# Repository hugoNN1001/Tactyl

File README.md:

# Tactyl

Tactyl is a gesture-based typing interface that lets you type anywhere without a keyboard. It converts finger taps into digital characters, avoiding the fixed workspace and repetitive wrist/hand positioning that conventional keyboards require.

## Photos

.jpg)

## How It Works

Tactyl uses a **five-bit chorded input** scheme: each of the five fingers acts as one bit. Tapping different finger combinations produces unique 5-bit codes, which are mapped in software to characters and commands. This gives 32 possible combinations enough to cover the full alphabet.

Finger movement is tracked by five IMUs (one per finger) embedded in the glove, allowing the system to distinguish intentional taps from general hand motion. Sensor data is processed by an ESP32-based embedded controller and transmitted wirelessly to a host computer. A haptic feedback system provides confirmation of typed characters and connection status.

## System Architecture

**Sensing layer.** Five **IMUs**, one per finger, each measuring acceleration to detect individual finger taps independently. Since they all share the same I²C address, a **TCA9548A I²C multiplexer** separates them into independent channels to faciliate communication.

**Power.** A **BQ24074 linear charge management IC** handles Li-ion battery charging while supporting system load via its **power-path output**. Charge current (300mA/500 mA) is selectable via solder jumpers. **Reverse polarity protection** is implemented with a P-FET with a **G-S protection diode**. The 3.3 V rail is generated by a **AP2112 LDO**. A **MAX17048 fuel gauge** monitors voltage/SOC over I²C and asserts an ALERT interrupt for **low-battery detection**, feeding the firmware's haptic alert logic. Main power traces were sized appropriate to handle the expected load. 

**Programming.** A **CP2102 USB-UART bridge** converts USB differential signals to UART to program the ESP32. Differential traces are kept short and **sized to 90Ω impedance**. ESD protection diodes are placed as close to the USB-C connector as possible.

**Processing.** An **ESP32-S3 microcontroller** processes sensor inputs, runs tap detection, maintains the five-bit finger state register, performs chord recognition, and manages communication with the host device. Each completed chord is looked up in a table and converted into the corresponding character. An **auto-program circuit** is also implemented with a pair to MOSFETs to automatically trigger BOOT & RST when programming.

**Wireless communication.** The interpreted character is transmitted over **Bluetooth Low Energy (BLE)** from the ESP32-S3 to the host device. The antenna keep-out section is kept clear of any copper.

**Haptic feedback.** A vibration motor, driven by a **DRV2605L haptic driver**, gives the user tactile confirmation of events such as BLE connection/disconnection state and low power. An **ERM coin vibration motor** is mounted through **strain-relief holes** on the main PCB. For the next version, a better decoupling capacitor should be added to prevent the ESP from resetting during strong motor vibrations.

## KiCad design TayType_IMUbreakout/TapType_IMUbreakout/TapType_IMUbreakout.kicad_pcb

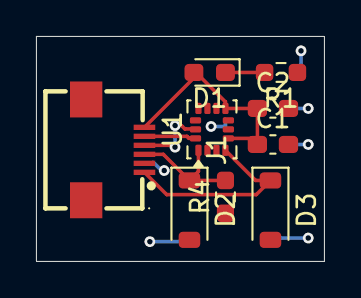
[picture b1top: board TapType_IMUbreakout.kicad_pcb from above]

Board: 2 copper layers, 16.0 x 12.5 mm, 9 parts (0 on the bottom side), 7 nets.

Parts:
C1, C2: 100nF; C_0603_1608Metric_Pad1.08x0.95mm_HandSolder
D1: LED; LED_0603_1608Metric_Pad1.05x0.95mm_HandSolder
D2, D3: SMF5.0A; D_SOD-123
J1: Conn_01x06; FPC-SMD_6P-P0.50_FPC-05FB-6PH20
R1: 220R; R_0603_1608Metric_Pad0.98x0.95mm_HandSolder
R4: 10k; R_0603_1608Metric_Pad0.98x0.95mm_HandSolder
U1: LSM6DS3; LGA-14_3x2.5mm_P0.5mm_LayoutBorder3x4y

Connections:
+3.3V: C1.1, C2.1, D1.2 (A), J1.6, U1.5 (VDDIO), U1.8 (VDD)
/INT1: D3.1, J1.1, U1.4 (INT1)
/SA0: D2.1, J1.3, R4.2, U1.1 (SDO/SA0)
/SCL: J1.4, U1.13 (SCL)
/SDA: J1.5, U1.14 (SDA)
GND: C1.2, C2.2, D2.2, D3.2, J1.2, R1.1, R4.1, U1.6 (GND), U1.7 (GND)
unnamed: D1.1 (K), R1.2

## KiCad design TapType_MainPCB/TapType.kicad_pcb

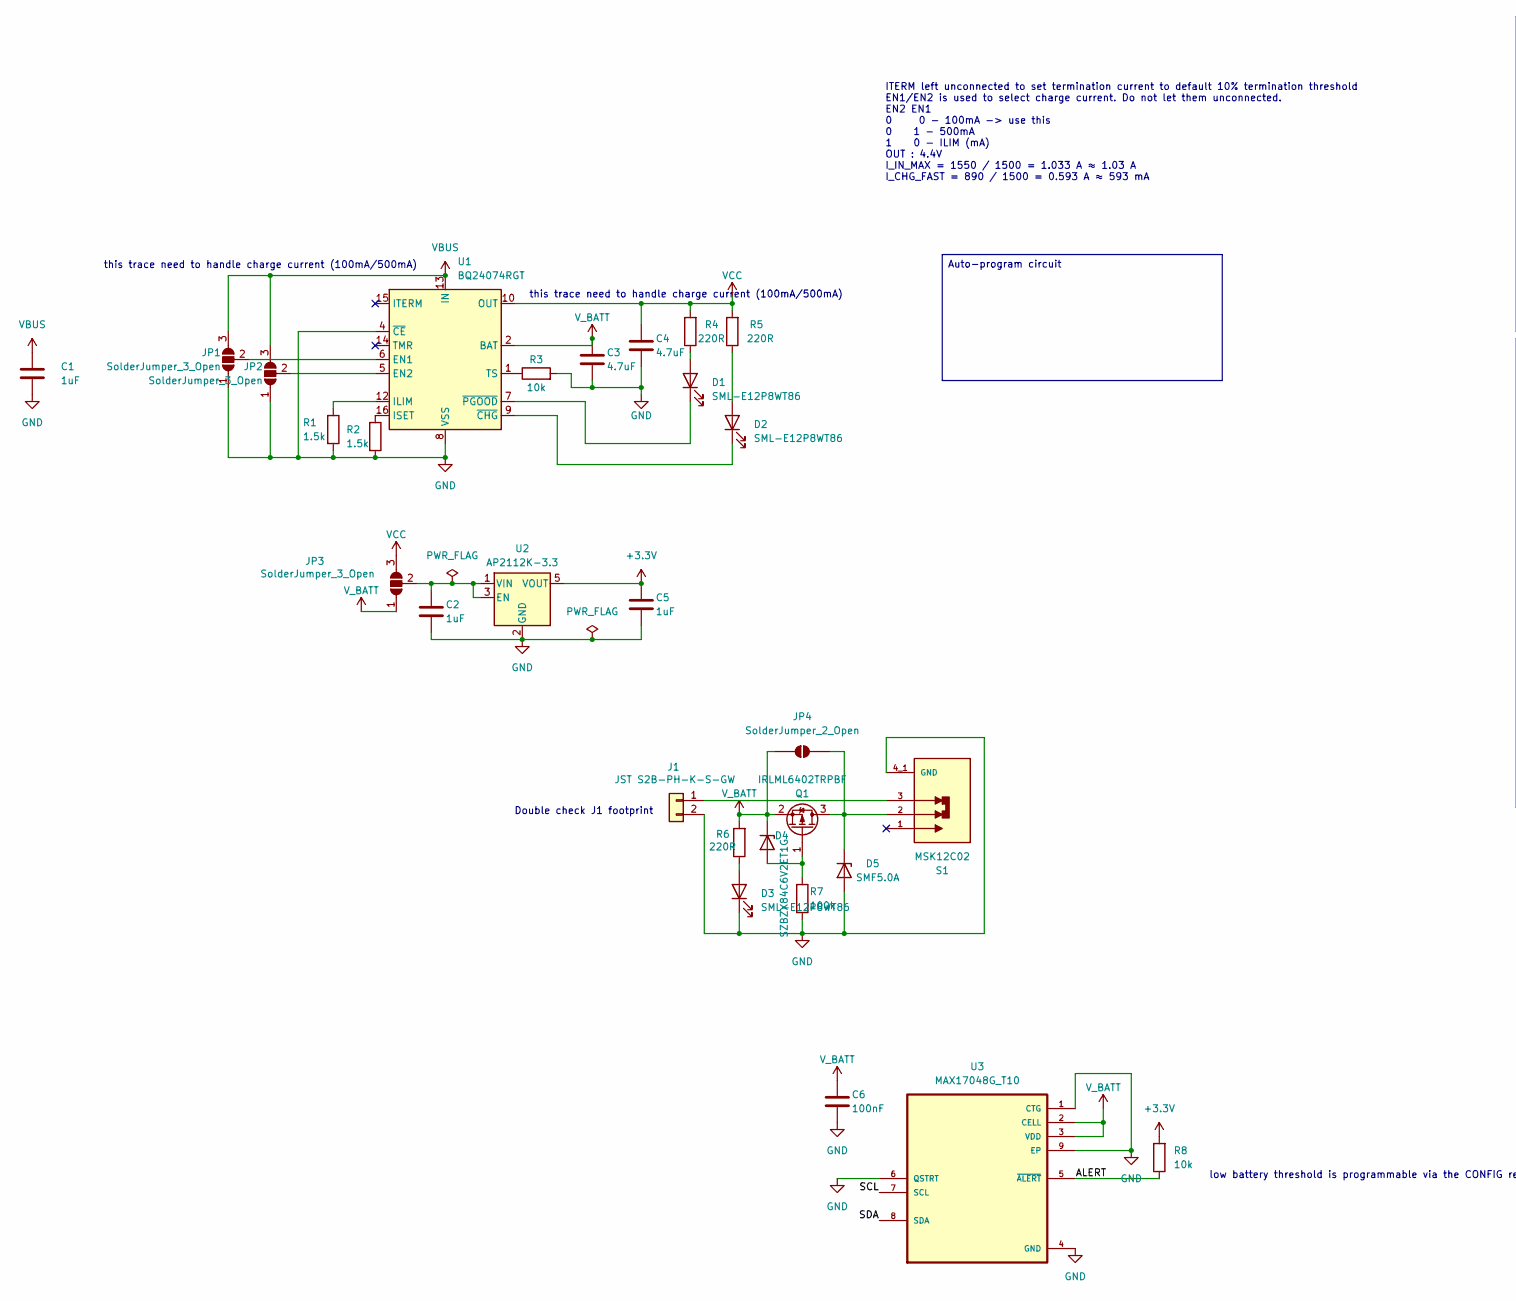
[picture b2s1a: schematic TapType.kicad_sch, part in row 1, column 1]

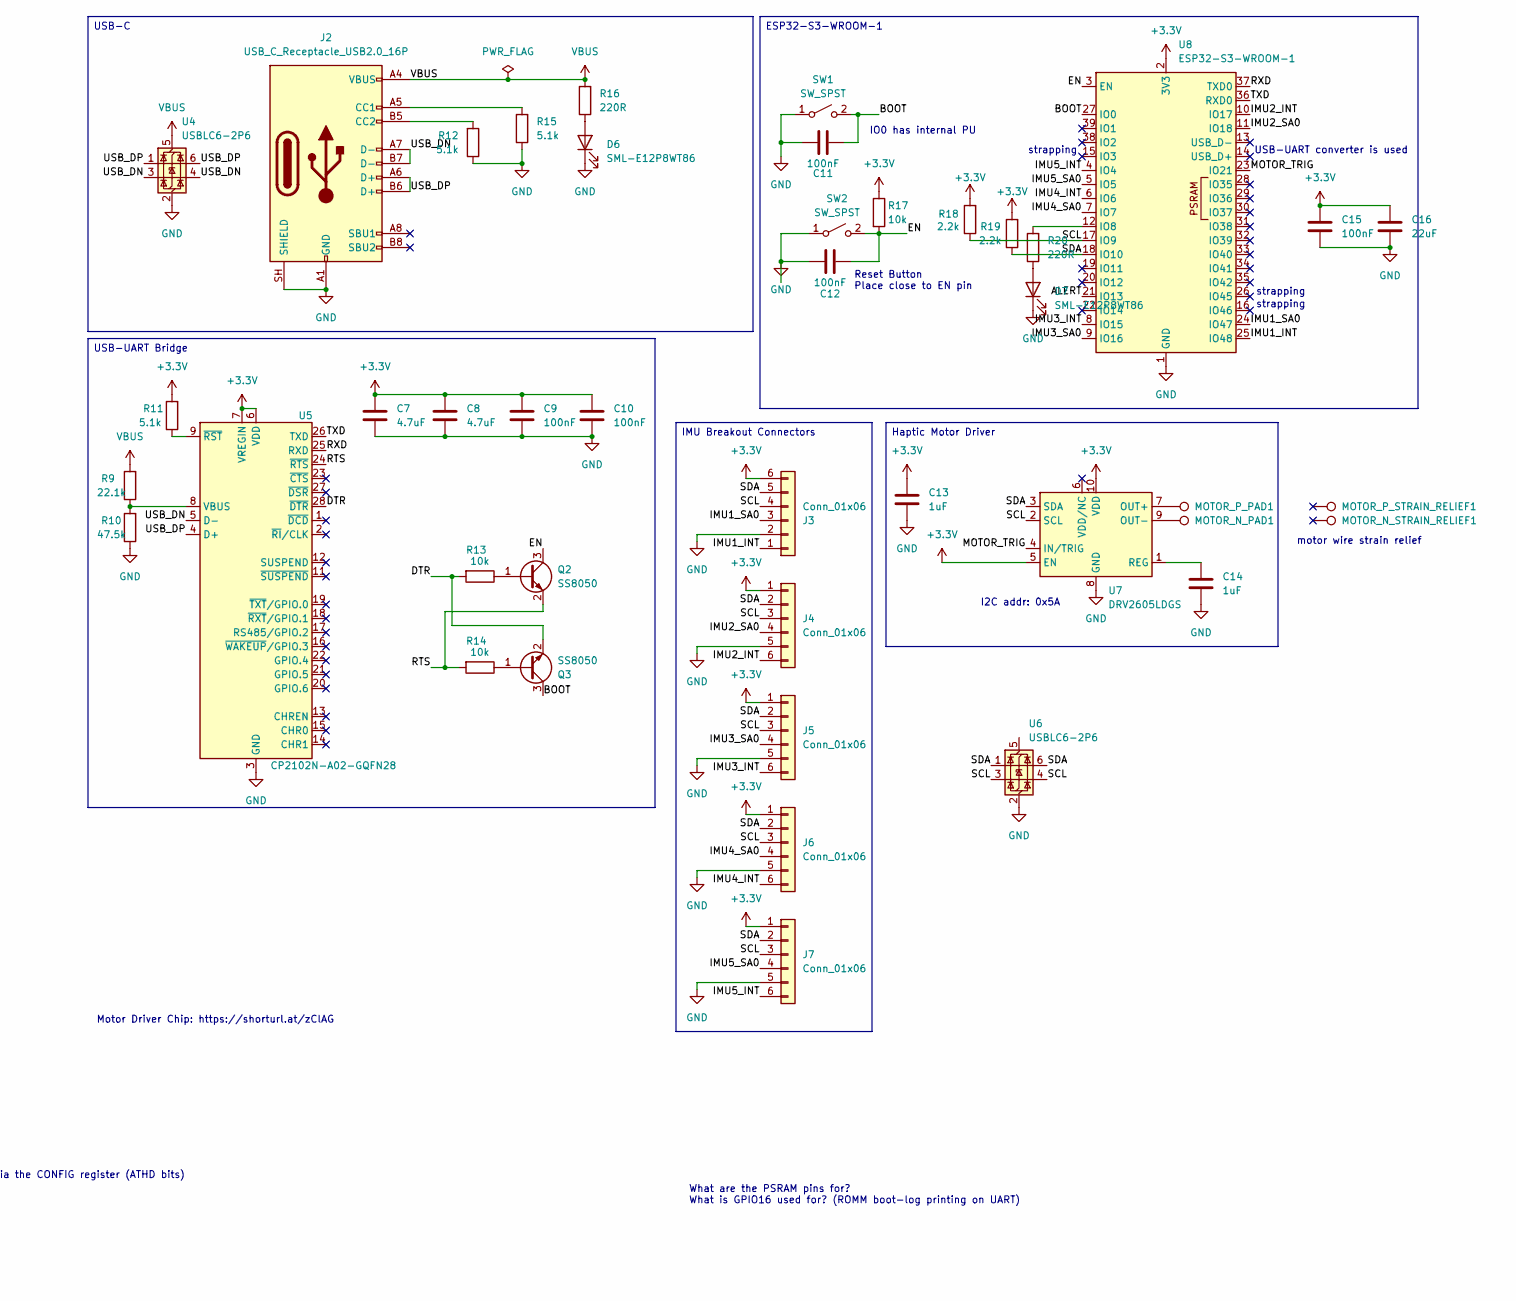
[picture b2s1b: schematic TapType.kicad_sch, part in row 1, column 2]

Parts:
C1, C2, C5, C13, C14: 1uF; C_0603_1608Metric
C3, C4, C7, C8: 4.7uF; C_0603_1608Metric
C6, C9, C10, C11, C12, C15: 100nF; C_0603_1608Metric
C16: 22uF; C_0603_1608Metric
D1, D2, D3, D6, D7: SML-E12P8WT86; D_0603_1608Metric
D4: SZBZX84C6V2ET1G; SOD-123_L2.7-W1.6-LS3.7-RD
D5: SMF5.0A; D_SOD-123F
J1: JST S2B-PH-K-S-GW; CONN-TH_S2B-PH-K-S-GW
J2: USB_C_Receptacle_USB2.0_16P; TYPE-C-SMD_SBC-160S1A-20-S412
J3, J4, J5, J6, J7: Conn_01x06; FPC-SMD_6P-P0.50_FPC-05FB-6PH20
JP1, JP2, JP3: SolderJumper_3_Open; SolderJumper-3_P2.0mm_Open_TrianglePad1.0x1.5mm
JP4: SolderJumper_2_Open; SolderJumper-2_P1.3mm_Open_TrianglePad1.0x1.5mm
MOTOR_N_PAD1: TestPoint; TestPoint_Pad_D2.0mm
MOTOR_N_STRAIN_RELIEF1: TestPoint; strain relief
MOTOR_P_PAD1: TestPoint; TestPoint_Pad_D2.0mm
MOTOR_P_STRAIN_RELIEF1: TestPoint; strain relief
Q1: IRLML6402TRPBF; SOT-23
Q2, Q3: SS8050; SOT-23
R1, R2: 1.5k; R_0603_1608Metric
R3, R8, R13, R14, R17: 10k; R_0603_1608Metric
R4, R5, R6, R16, R20: 220R; R_0603_1608Metric
R7: 100k; R_0603_1608Metric
R9: 22.1k; R_0603_1608Metric
R10: 47.5k; R_0603_1608Metric
R11, R12, R15: 5.1k; R_0603_1608Metric
R18, R19: 2.2k; R_0603_1608Metric
S1: MSK12C02; SW-SMD_G-SWITCH_MK-12C02-G015; PARTREV A/0
SW1, SW2: SW_SPST; KEY-SMD_B3U-1000PM
U1: BQ24074RGT; VQFN-16-1EP_3x3mm_P0.5mm_EP1.6x1.6mm
U2: AP2112K-3.3; SOT-23-5
U3: MAX17048G_T10; SON50P200X200X80-9N
U4, U6: USBLC6-2P6; SOT-666
U5: CP2102N-A02-GQFN28; QFN-28-1EP_5x5mm_P0.5mm_EP3.35x3.35mm
U7: DRV2605LDGS; TSSOP-10_3x3mm_P0.5mm
U8: ESP32-S3-WROOM-1

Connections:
+3.3V: C5.1, C7.1, C8.1, C9.1, C10.1, C13.1, C15.1, C16.1, J3.6, J4.1, J5.1, J6.1, J7.1, R8.2, R11.2, R17.1, R18.2, R19.2, U2.5 (VOUT), U5.6 (VDD), U5.7 (VREGIN), U7.5 (EN), U7.10 (VDD), U8.2 (3V3)
/ALERT: R8.1, U3.5 (~ALERT), U8.21 (IO13)
/BOOT: C11.2, Q3.3 (C), SW1.2 (B), U8.27 (IO0); also elsewhere on the board
/DTR: Q3.2 (E), R13.2, U5.28 (~DTR)
/EN: C12.1, Q2.3 (C), R17.2, SW2.2 (B), U8.3 (EN); also elsewhere on the board
/IMU1_INT: J3.1, U8.25 (IO48)
/IMU1_SA0: J3.3, U8.24 (IO47)
/IMU2_INT: J4.6, U8.10 (IO17)
/IMU2_SA0: J4.4, U8.11 (IO18)
/IMU3_INT: J5.6, U8.8 (IO15)
/IMU3_SA0: J5.4, U8.9 (IO16)
/IMU4_INT: J6.6, U8.6 (IO6)
/IMU4_SA0: J6.4, U8.7 (IO7)
/IMU5_INT: J7.6, U8.4 (IO4)
/IMU5_SA0: J7.4, U8.5 (IO5)
/MOTOR_TRIG: U7.4 (IN/TRIG), U8.23 (IO21)
/RTS: Q2.2 (E), R14.2, U5.24 (~RTS)
/RXD: U5.25 (RXD), U8.37 (TXD0)
/SCL: J3.4, J4.3, J5.3, J6.3, J7.3, R18.1, U3.7 (SCL), U6.3 (I/O2), U6.4 (I/O2), U7.2 (SCL), U8.17 (IO9)
/SDA: J3.5, J4.2, J5.2, J6.2, J7.2, R19.1, U3.8 (SDA), U6.1 (I/O1), U6.6 (I/O1), U7.3 (SDA), U8.18 (IO10)
/TXD: U5.26 (TXD), U8.36 (RXD0)
/USB_DN: J2.A7 (D-), J2.B7 (D-), U4.3 (I/O2), U4.4 (I/O2), U5.5 (D-)
/USB_DP: J2.A6 (D+), J2.B6 (D+), U4.1 (I/O1), U4.6 (I/O1), U5.4 (D+)
GND: C1.2, C2.2, C3.2, C4.2, C5.2, C6.2, C7.2, C8.2, C9.2, C10.2, C11.1, C12.2, C13.2, C14.2, C15.2, C16.2, D3.1 (K), D5.2 (A), D6.1 (K), D7.1 (K), J1.2, J2.A1 (GND), J2.A12 (GND), J2.B1 (GND), J2.B12 (GND), J2.SH (SHIELD), J3.2, J4.5, J5.5, J6.5, J7.5, JP1.1 (A), JP2.1 (A), R1.2, R2.2, R3.2, R7.2, R10.1, R12.1, R15.1, S1.4_1 (GND), S1.4_2 (GND), S1.4_3 (GND), S1.4_4 (GND), SW1.1 (A), SW2.1 (A), U1.4 (~CE), U1.8 (VSS), U1.17 (VSS), U2.2 (GND), U3.1 (CTG), U3.4 (GND), U3.6 (QSTRT), U3.9 (EP), U4.2 (GND), U5.3 (GND), U5.29 (GND), U6.2 (GND), U7.8 (GND), U8.1 (GND), U8.40 (GND), U8.41 (GND); also elsewhere on the board
unnamed: D1.2 (A), R4.1
unnamed: D1.1 (K), U1.7 (~PGOOD)
unnamed: D2.2 (A), R5.1
unnamed: D2.1 (K), U1.9 (~CHG)
unnamed: D3.2 (A), R6.1
unnamed: D4.1 (A_1), Q1.1 (G), R7.1
unnamed: D5.1 (K), JP4.1 (A), Q1.3 (D), S1.2
unnamed: D6.2 (A), R16.1
unnamed: D7.2 (A), R20.1
unnamed: J1.1, S1.3
unnamed: J2.A5 (CC1), R15.2
unnamed: J2.B5 (CC2), R12.2
unnamed: JP1.2 (C), U1.6 (EN1)
unnamed: JP2.2 (C), U1.5 (EN2)
unnamed: C2.1, JP3.2 (C), U2.1 (VIN), U2.3 (EN)
unnamed: Q2.1 (B), R13.1
unnamed: Q3.1 (B), R14.1
unnamed: R1.1, U1.12 (ILIM)
unnamed: R2.1, U1.16 (ISET)
unnamed: R3.1, U1.1 (TS)
unnamed: R9.1, R10.2, U5.8 (VBUS)
unnamed: R11.1, U5.9 (~RST)
unnamed 46: MOTOR_P_PAD1.1, U7.7 (OUT+); also elsewhere on the board
unnamed 47: MOTOR_N_PAD1.1, U7.9 (OUT-); also elsewhere on the board
unnamed: C14.1, U7.1 (REG)
unnamed: R20.2, U8.12 (IO8)
VBUS: C1.1, J2.A4 (VBUS), J2.A9 (VBUS), J2.B4 (VBUS), J2.B9 (VBUS), JP1.3 (B), JP2.3 (B), R9.2, R16.2, U1.13 (IN), U4.5 (VBUS)
VCC: C4.1, JP3.3 (B), R4.2, R5.2, U1.10 (OUT), U1.11 (OUT)
V_BATT: C3.1, C6.1, D4.3 (K), JP3.1 (A), JP4.2 (B), Q1.2 (S), R6.2, U1.2 (BAT), U1.3 (BAT), U3.2 (CELL), U3.3 (VDD)

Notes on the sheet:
motor wire strain relief
this trace need to handle charge current (100mA/500mA)
low battery threshold is programmable via the CONFIG register (ATHD bits)
USB-UART converter is used
strapping
ITERM left unconnected to set termination current to default 10% termination threshold EN1/EN2 is used to select charge current. Do not let them unconnected. EN2 EN1 0 0 - 100mA -> use this 0 1 - 500mA 1 0 - ILIM (mA) OUT : 4.4V I_IN_MAX = 1550 / 1500 = 1.033 A ≈ 1.03 A I_CHG_FAST = 890 / 1500 = 0.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
Double check J1 footprint
What are the PSRAM pins for? What is GPIO16 used for? (ROMM boot-log printing on UART)
I2C addr: 0x5A
IO0 has internal PU
Motor Driver Chip: https://shorturl.at/zClAG
Reset Button Place close to EN pin
USB-UART Bridge
Haptic Motor Driver
ESP32-S3-WROOM-1
IMU Breakout Connectors
Auto-program circuit
USB-C

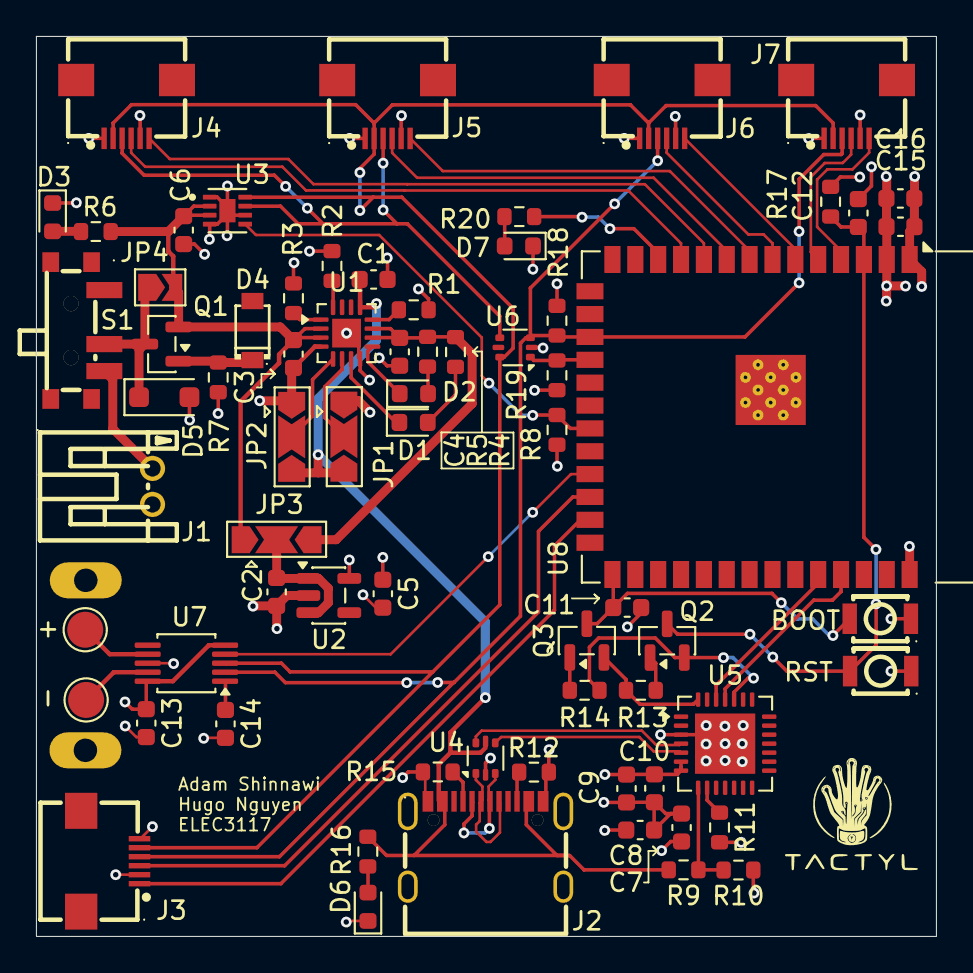
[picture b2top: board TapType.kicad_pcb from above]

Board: 4 copper layers, 50.0 x 50.0 mm, 72 parts (0 on the bottom side), 53 nets.

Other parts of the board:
+: TestPoint; TestPoint_Pad_D2.0mm
-: TestPoint; TestPoint_Pad_D2.0mm
BOOT: SW_SPST; KEY-SMD_B3U-1000PM
RST: SW_SPST; KEY-SMD_B3U-1000PM

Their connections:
/BOOT: BOOT.2 (B); also elsewhere on the board
/EN: RST.2 (B); also elsewhere on the board
GND: BOOT.1 (A), RST.1 (A); also elsewhere on the board
unnamed 46: +.1 (1_1); also elsewhere on the board
unnamed 47: -.1 (1_1); also elsewhere on the board
